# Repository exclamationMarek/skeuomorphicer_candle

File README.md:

# Skeuomorphicer Candle

A more skeuomorphic LED candle, one that you turn on with a flame, and off with a blow, like a real candle!
Super simple design with no microcontrollers, op-amps nor any other integrated circuits. Just one transistor, one thermistor and a couple of passives.

As seen on youtube, here: [https://www.youtube.com/watch?v=r8O8MNvkZiY](https://www.youtube.com/watch?v=r8O8MNvkZiY)

# How it works

* Heating the NTC thermistor makes its resistance drop, which increases the voltage on the MOSFET gate and turns on the bulb
* The current limiting R2 resistor gets hot
* The PCB is carefully designed to thermally connect R2 to the NTC
* Heat from R2 makes the NTC hot, so it stays hot even when the flame is removed
* This keeps the candle on
* Once you blow on the PCB, the heat is removed, breaking the cycle and turning off the light
* Yes, the schematic looks like a candle

* The current limiting (and heat producing) resistor is doubled, to surround the NTC on both sides
* They also share an electrical connection with the NTC - the VCC node (on top)
* That VCC copper connection is used to transfer heat from the resistors to the NTC
* But also, is wide and exposed to being blown at
* This is a finicky design challenge that required iterative fine tuning
* The current implementation works best with about 0.1W (total) dissipated on the heating resistors, which keeps the NTC at about 55°C
* Testd on a 1.0mm 2-layer PCB with 35um copper foil. Tested with black solder mask (it might make a difference?)

Note that this is the simplified schematic that omits the power supply. In real application, the varying voltage of batteries causes the circuit to be unreliable. With a full battery, the NTC runs too hot, making the candle difficult to blow out, and with a low battery it runs too cool, turning itself off unprompted. To fix this, the recommended design adds a voltage regulator (boost converter) to keep VCC stable and the candle reliable.

# PCB design available in 4 variants:
## [Minimal](Skeuomorphic_candle_minimal)
* Designed for 1.5V mini light bulb and 2xAA batteries
* Very low component count
* Does not work with LEDs!
* No ICs. Just 1 NMOS, 1 NTC and some resistors
* If you want the simplest skeuomorphicer candle, use this PCB.
* Alternatively, use with external 3.3V regulated supply

## [Basic - recommended](Skeuomorphic_candle_basic)
* Works great with a mini light bulb and OK-ish with LEDs
* Supports various batteries
* Low component count, but requires power regulator IC
* If you want to make a resonably well working skeuomorphicer candle, use this PCB

## [Custom](Skeuomorphic_candle_custom)
* PCB with extra footprints for implementation flexibility
* Can be configured as either the "Minimal" or "Basic" variant
* Can be configured as bulb + LEDs
* LED brightness can be adjusted, while maintaining reliable flame detection
* Has test points
* If you want to experiment with the design, use this PCB

## [Digital](Skeuomorphic_candle_digital)
* EWWWW digital microcontroller!
* 32bits?! For like one 'if' statement?!
* 2KB of RAM?! You can fly to the bloody moon on 2KB of RAM!
* If you're one of those futuristic cyberpunk chooms, use this PCB. I will try not to cry.

Detailed configuration and assembly instructions are in each PCB variant folder.

# License
This project is published under the [Creative Commons Attribution-NonCommercial 4.0 License](https://creativecommons.org/licenses/by-nc/4.0/deed.en)

Full text in license.txt

A commertial use license may be provided upon request

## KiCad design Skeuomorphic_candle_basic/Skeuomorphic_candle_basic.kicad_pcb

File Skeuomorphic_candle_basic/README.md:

# Basic Skeuomorphicer Candle
Most recommended design

# UNTESTED!
As of releasing this repo, this exact PCB design is NOT TESTED. It might be all wrong. I'm still waiting for this revision of PCBs to arrive to my lab.

# Part list (light bulb configuration)
* 1x 1.5V miniature tungsten bulb. Should draw about 100-130mA at 1.5V
* 1x SI2302 N-MOS (or similar)
* 1x ETA1061V33 boost converter with 3.3V output
* 1x 2.2uH inductor in 1008 package
* 2x 4.7uF capacitors in 0603 package
* 1x 100k NTC in 0603 package
* 2x 33R resistors in 0603 package
* 1x 6.8k resistor in 0603 package
* 1x battery holder for 2xAA
* 2x AA battery (NiMH rechargable works great)

# PCB configuration:
* 2-layer
* 1.0mm thick
* 35um (1oz) copper foil
* Basic FR4 TG135 (The candle is a bad idea and fire hazard no matter what material you pick)
* Soldermask colour may affect performance due to different emissivity. I used black to make it look like a wick.

# Assembly manual (light bulb configuration)
* Bridge Jumper JP1
* Skip D1
* Place 1.5V bulb on D2
* Use 3v3 out regulator for U1
* Populate all other components as listed in the schematic
* Find a value of R1 that makes candle work well. REDUCE if hard to blow out, INCREASE if does not stay on
* Supply from 2xAA or 2xAAA batteries
* Technically should also work with 1xAA

# Assembly manual (LED configuration)
* Use a 5V out regulator for U1
* Open Jumper JP1
* Place 2x LEDs on D1 and D2
* Populate R2 and R3 with 47-100R. Higher value produces dimmer light, but also less heat for the heat detection circut
* Populate all other components as listed in the schematic
* Find a value of R1 that makes candle work well. REDUCE if hard to blow out, INCREASE if does not stay on
* Supply from 2x or 3x AA or AAA batteries
* Technically should also work with 1xAA
* The 'custom' variant of the PCB separates the heaters from the LED current limiting resistors, which allows for dim light and reliable heat control

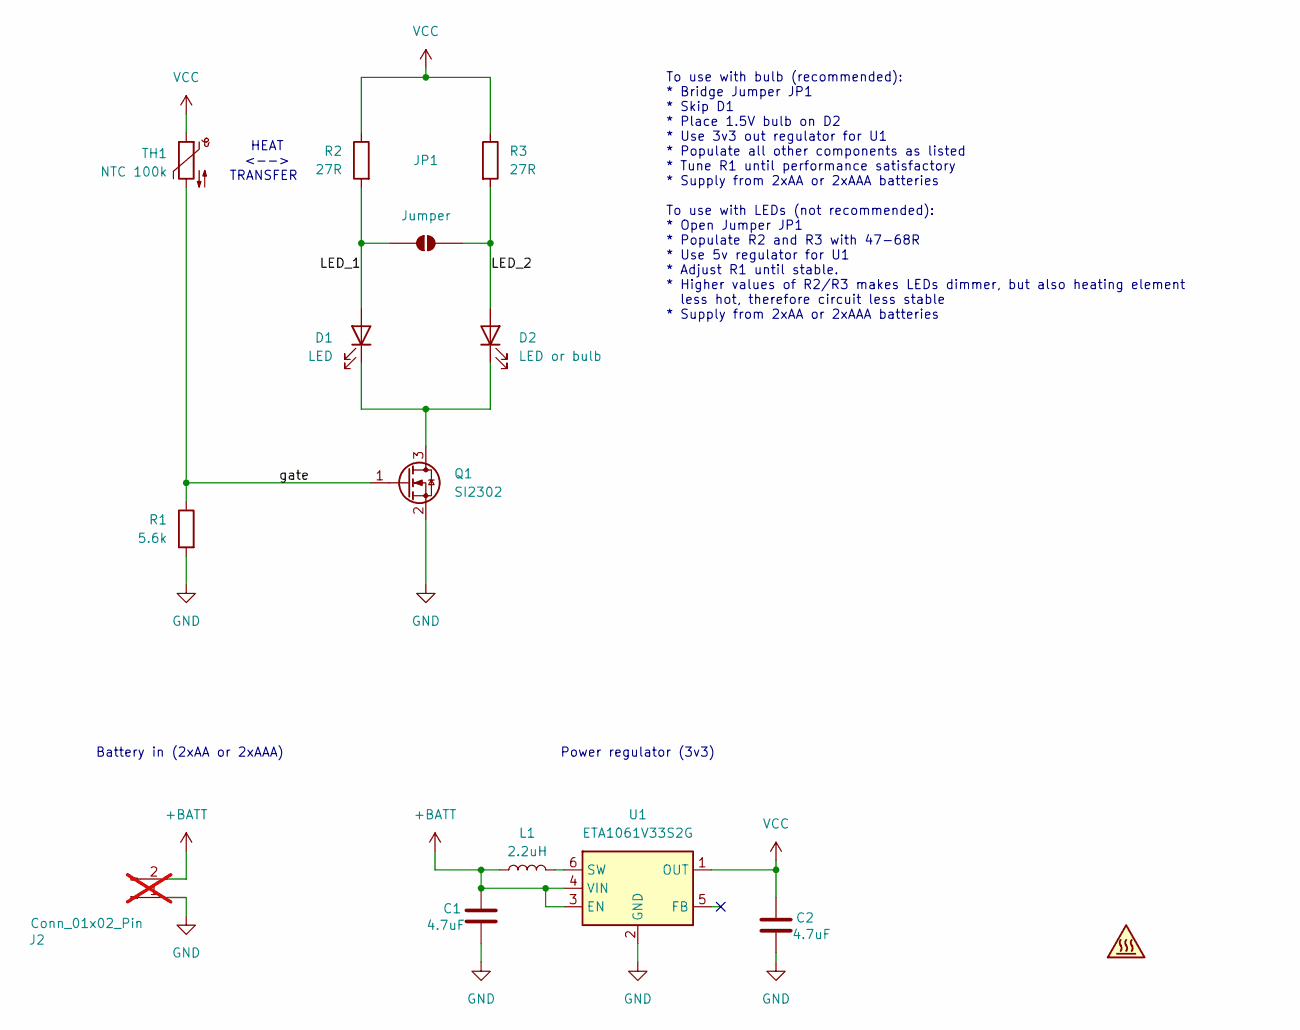
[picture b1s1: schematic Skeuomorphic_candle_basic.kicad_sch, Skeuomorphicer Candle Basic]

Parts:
C1, C2: 4.7uF; C_0603_1608Metric_Pad1.08x0.95mm_HandSolder
D1: LED; LED_PLCC_2835_Handsoldering
D2: LED or bulb; LED_PLCC_2835_Handsoldering
J2: Conn_01x02_Pin; PinHeader_1x02_P2.54mm_Vertical; not fitted
JP1: Jumper; SolderJumper-2_P1.3mm_Open_RoundedPad1.0x1.5mm
L1: 2.2uH; L_1008_2520Metric_Pad1.43x2.20mm_HandSolder; MPN WIP252012P-2R2ML
LOGO1: Logo; Skeuomorphicer_candle_logo
Q1: SI2302; SOT-23-handsoldering-smaller
R1: 5.6k; R_0603_1608Metric_Pad0.98x0.95mm_HandSolder
R2, R3: 27R; R_0603_1608Metric_Pad0.98x0.95mm_HandSolder
TH1: NTC 100k; R_0603_1608Metric_Pad0.98x0.95mm_HandSolder
U1: ETA1061V33S2G; SOT-23-6

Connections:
+BATT: C1.1, J2.2, L1.1, U1.3 (EN), U1.4 (VIN)
/LED_1: D1.2 (A), JP1.1 (A), R2.2
/LED_2: D2.2 (A), JP1.2 (B), R3.2
/gate: Q1.1 (G), R1.1, TH1.2
GND: C1.2, C2.2, J2.1, Q1.2 (S), R1.2, U1.2 (GND)
unnamed: D1.1 (K), D2.1 (K), Q1.3 (D)
unnamed: L1.2, U1.6 (SW)
VCC: C2.1, R2.1, R3.1, TH1.1, U1.1 (OUT)

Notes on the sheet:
To use with bulb (recommended): * Bridge Jumper JP1 * Skip D1 * Place 1.5V bulb on D2 * Use 3v3 out regulator for U1 * Populate all other components as listed * Tune R1 until performance satisfactory * Supply from 2xAA or 2xAAA batteries To use with LEDs (not recommended): * Open Jumper JP1 * Popul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
HEAT <--> TRANSFER
Battery in (2xAA or 2xAAA)
Power regulator (3v3)

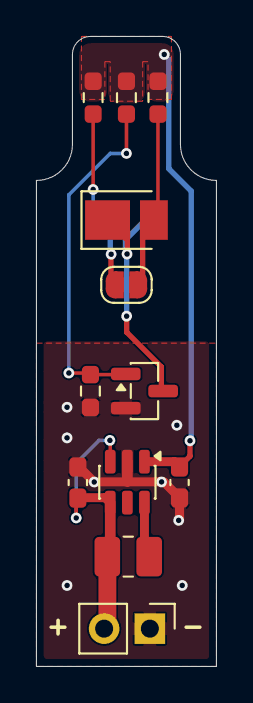
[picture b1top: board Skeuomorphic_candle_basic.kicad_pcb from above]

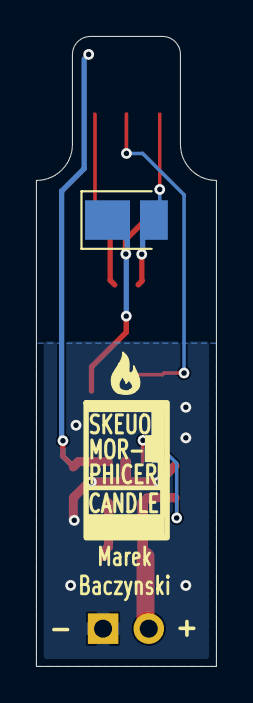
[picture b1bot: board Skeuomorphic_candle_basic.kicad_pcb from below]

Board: 2 copper layers, 10.0 x 35.0 mm, 14 parts (2 on the bottom side), 8 nets.

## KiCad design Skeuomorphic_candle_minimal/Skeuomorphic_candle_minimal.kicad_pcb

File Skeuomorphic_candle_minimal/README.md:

# Minimal Skeuomorphicer Candle
Wokrs OK, not great, but uses very few parts

# Assembly instructions

* Populate all components as shown
* Supply from 2xAA batteries (NiMH rechargable preferably)
* Test if behaves well
* If does not stay on, increase R1 (27k)
* If difficult to blow out, reduce R1 (27k)

# Sensitive to battery voltage
* This design is sensitive to battery voltage
* The lower the voltage, the more likely the candle will turn itself off
* Therefore, the candle will likely turn itself off even then there is plenty of energy left in the battery
* That is why it is best to use NiMH rechargables, otherwise you will be left with a buch of half-full batteries
* The other designs use a voltage regulator to avoid this issue

# Design relies of Vgs(th)
* This design relies on the threshold voltage of an NMOS, which is not good practice
* Be prepared to need to adjust R1 depending on your exact transistor
* It might even be necessary to tune for each transistor from the same batch
* Not a great design!

# Part list
* 1x 1.5V miniature tungsten bulb. 3mm or 4mm size, should draw about 130-160mA at 1.5V
* 1x SI2302 N-MOS (or similar. Vgs(th) should be about 0.7V)
* 1x 100k NTC thermistor in 0603 package
* 2x 22R resistors in 0603 package
* 1x 27k resistor in 0603 package
* 1x battery holder for 2xAA
* 2x AA battery (NiMH rechargable works great)

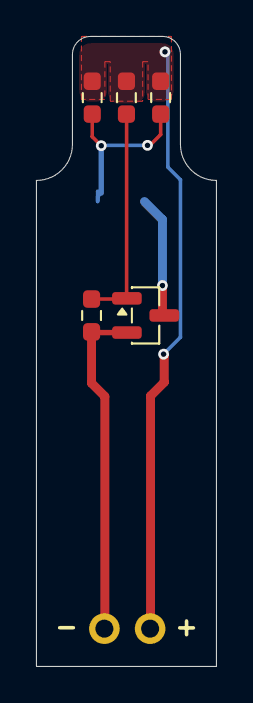
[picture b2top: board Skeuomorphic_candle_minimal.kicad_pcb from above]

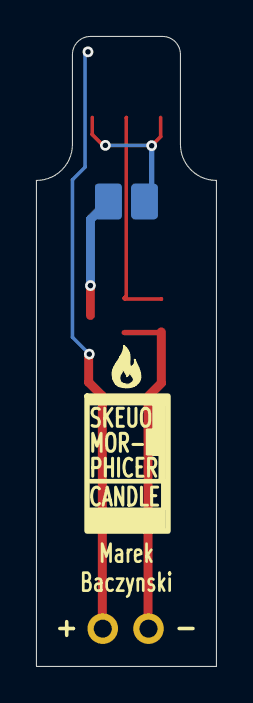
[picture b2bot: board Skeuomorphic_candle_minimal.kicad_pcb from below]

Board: 2 copper layers, 10.0 x 35.0 mm, 8 parts (2 on the bottom side), 5 nets.

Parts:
D1: BULB; Mini_bulb_flat
J2: Conn_01x02_Pin; PinHeader_1x02_P2.54mm_Vertical
LOGO1: Logo; Skeuomorphicer_candle_logo
Q1: SI2302; SOT-23-handsoldering-smaller
R1: 27k; R_0603_1608Metric_Pad0.98x0.95mm_HandSolder
R2, R3: 11R; R_0603_1608Metric_Pad0.98x0.95mm_HandSolder
TH1: NTC 100k; R_0603_1608Metric_Pad0.98x0.95mm_HandSolder

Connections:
+BATT: J2.2, R2.1, R3.1, TH1.1
/NTC_low: Q1.1 (G), R1.1, TH1.2
GND: J2.1, Q1.2 (S), R1.2
unnamed: D1.2 (A), R2.2, R3.2
unnamed: D1.1 (K), Q1.3 (D)

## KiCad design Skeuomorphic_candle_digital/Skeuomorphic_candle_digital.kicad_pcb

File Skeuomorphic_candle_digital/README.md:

# Digital Skeuomorphicer Candle
For when you just have to put code into everything

# UNTESTED!
As of releasing this repo, this PCB design is NOT TESTED. It might be all wrong.

# Part list
* CH32V003J4M6 microcontroller in SOP-8 package
* 100k NTC in 0603
* SI2302 NMOS (or similar)
* 1uF capacitor in 0603 for the MCU
* 3V miniature tungsten bulb, or 2x 2835 LEDs
* Some 0603 resistors
* Optionally some 0603 LEDs
* 3xAA or 3xAAA battery holder or 1x LiPo battery

# Firmware
Firmware for the Digital Skeuomorphicer Candle is comming soon. Probably.

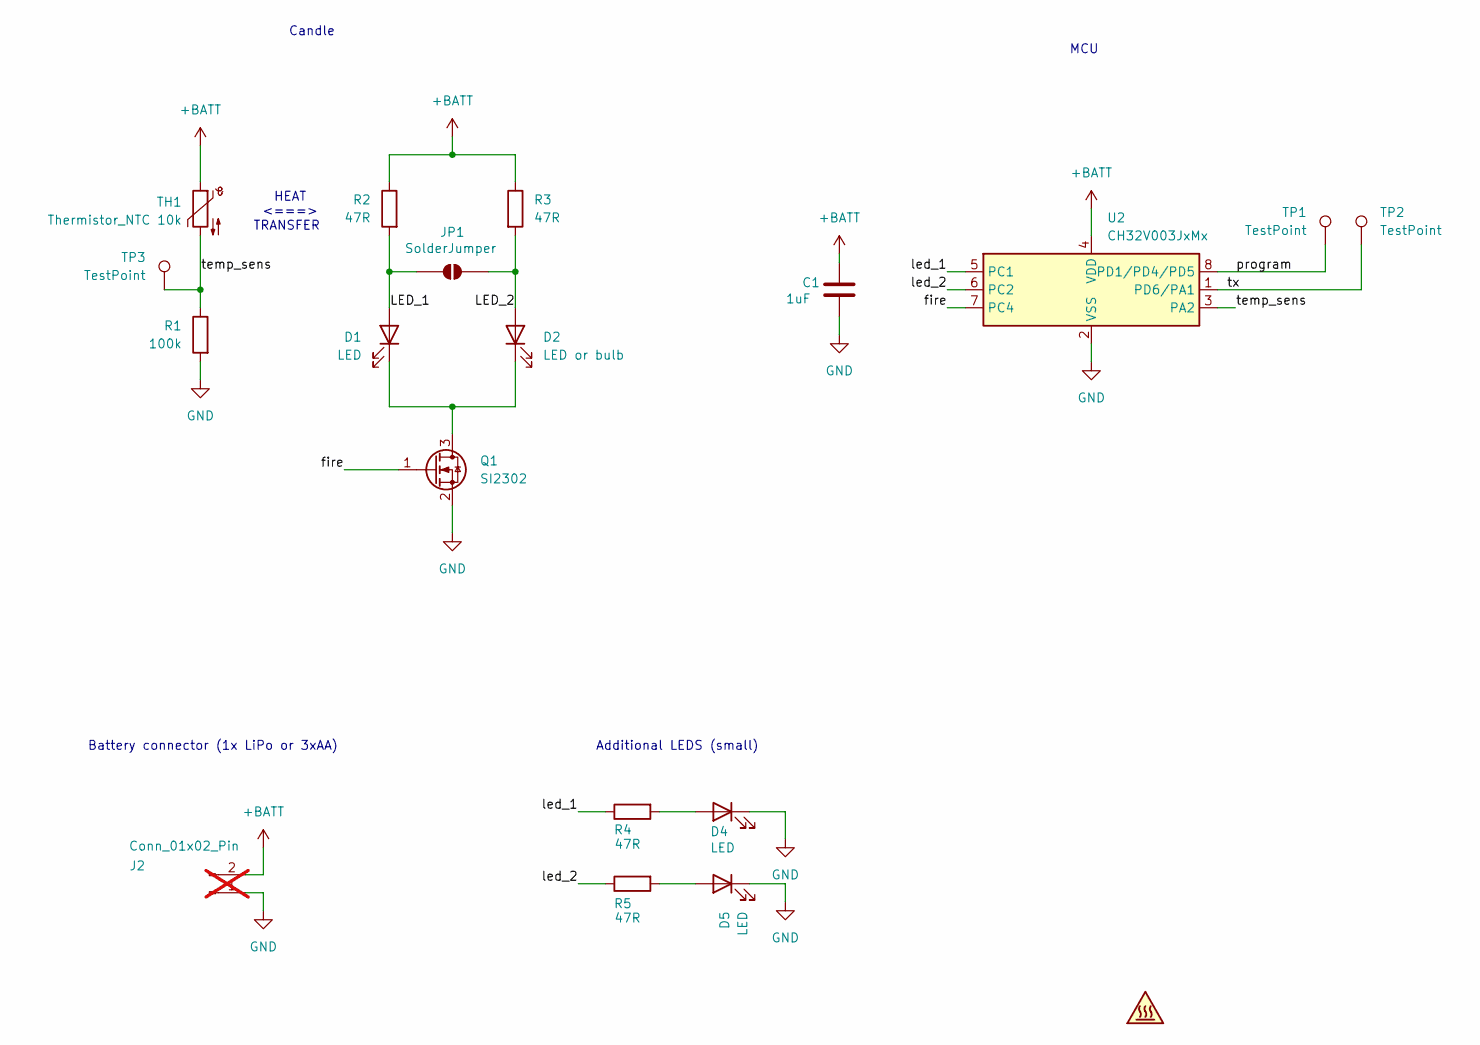
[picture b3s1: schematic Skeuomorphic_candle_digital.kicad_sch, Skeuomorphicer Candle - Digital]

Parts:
C1: 1uF; C_0603_1608Metric_Pad1.08x0.95mm_HandSolder
D1: LED; LED_PLCC_2835_Handsoldering
D2: LED or bulb; LED_PLCC_2835_Handsoldering
D4, D5: LED; LED_0603_1608Metric_Pad1.05x0.95mm_HandSolder
J2: Conn_01x02_Pin; PinHeader_1x02_P2.54mm_Vertical; not fitted
JP1: SolderJumper; SolderJumper-2_P1.3mm_Open_RoundedPad1.0x1.5mm
LOGO1: Logo; Skeuomorphicer_candle_logo
Q1: SI2302; SOT-23-handsoldering-smaller
R1: 100k; R_0603_1608Metric_Pad0.98x0.95mm_HandSolder
R2, R3, R4, R5: 47R; R_0603_1608Metric_Pad0.98x0.95mm_HandSolder
TH1: Thermistor_NTC 10k; R_0603_1608Metric_Pad0.98x0.95mm_HandSolder
TP1, TP2, TP3: TestPoint; TestPoint_Pad_D1.0mm
U2: CH32V003JxMx; JEITA_SOIC-8_3.9x4.9mm_P1.27mm

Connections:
+BATT: C1.1, J2.2, R2.1, R3.1, TH1.1, U2.4 (VDD)
/LED_1: D1.2 (A), JP1.1 (A), R2.2
/LED_2: D2.2 (A), JP1.2 (B), R3.2
/fire: Q1.1 (G), U2.7 (PC4)
/led_1: R4.1, U2.5 (PC1)
/led_2: R5.1, U2.6 (PC2)
/program: TP1.1 (1_1), U2.8 (PD1/PD4/PD5)
/temp_sens: R1.1, TH1.2, TP3.1 (1_1), U2.3 (PA2)
/tx: TP2.1 (1_1), U2.1 (PD6/PA1)
GND: C1.2, D4.1 (K), D5.1 (K), J2.1, Q1.2 (S), R1.2, U2.2 (VSS)
unnamed: D1.1 (K), D2.1 (K), Q1.3 (D)
unnamed: D4.2 (A), R4.2
unnamed: D5.2 (A), R5.2

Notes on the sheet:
MCU
Battery connector (1x LiPo or 3xAA)
HEAT <===> TRANSFER
Additional LEDS (small)
Candle

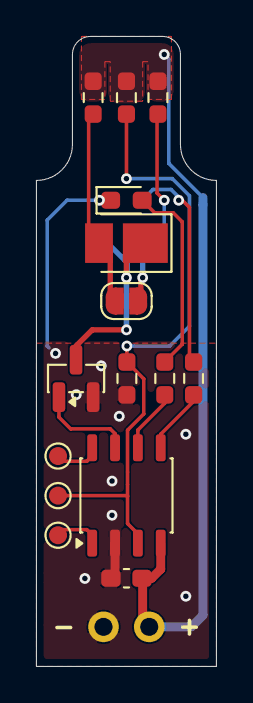
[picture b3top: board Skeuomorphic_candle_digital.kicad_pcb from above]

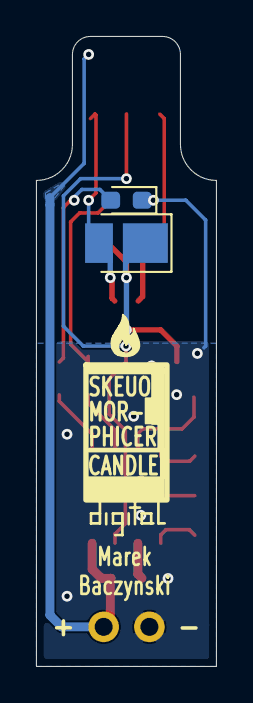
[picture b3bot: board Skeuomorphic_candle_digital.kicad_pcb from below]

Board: 2 copper layers, 10.0 x 35.0 mm, 19 parts (3 on the bottom side), 13 nets.

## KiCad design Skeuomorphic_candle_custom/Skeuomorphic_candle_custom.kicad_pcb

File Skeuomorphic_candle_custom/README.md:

# Custom Skeuomorphicer Candle
For when you want to experiment with the design

# UNTESTED!
As of releasing this repo, this PCB design is NOT TESTED. It might be all wrong.

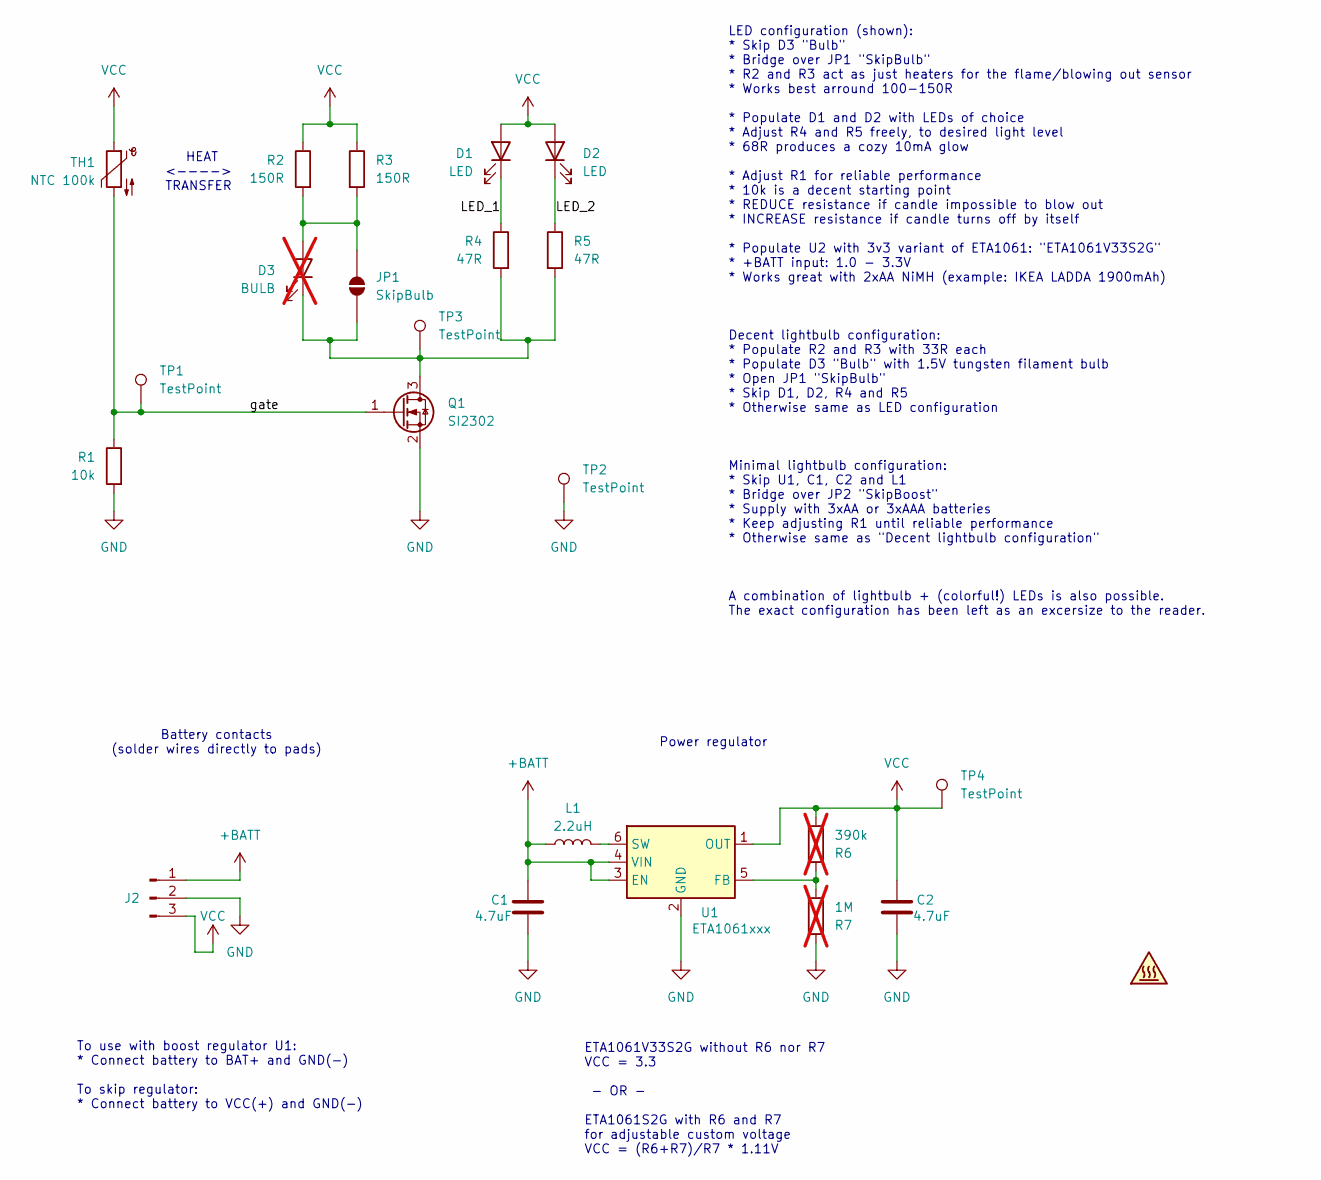
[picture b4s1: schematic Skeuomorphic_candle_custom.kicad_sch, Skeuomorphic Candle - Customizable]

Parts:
C1, C2: 4.7uF; C_0603_1608Metric_Pad1.08x0.95mm_HandSolder
D1, D2: LED; LED_PLCC_2835_Handsoldering
D3: BULB; Mini_bulb_flat; not fitted
J2: Conn_01x03_Pin; PinHeader_1x03_P2.54mm_Vertical
JP1: SkipBulb; SolderJumper-2_P1.3mm_Open_RoundedPad1.0x1.5mm
L1: 2.2uH; L_1008_2520Metric_Pad1.43x2.20mm_HandSolder; MPN INPAQ WIP252012P-2R2ML
LOGO1: Logo; Skeuomorphicer_candle_logo
Q1: SI2302; SOT-23-handsoldering-smaller
R1: 10k; R_0603_1608Metric_Pad0.98x0.95mm_HandSolder
R2, R3: 150R; R_0603_1608Metric_Pad0.98x0.95mm_HandSolder
R4, R5: 47R; R_0603_1608Metric_Pad0.98x0.95mm_HandSolder
R6: 390k; R_0603_1608Metric_Pad0.98x0.95mm_HandSolder; not fitted
R7: 1M; R_0603_1608Metric_Pad0.98x0.95mm_HandSolder; not fitted
TH1: NTC 100k; R_0603_1608Metric_Pad0.98x0.95mm_HandSolder
TP1, TP2, TP3, TP4: TestPoint; TestPoint_Pad_D1.0mm
U1: ETA1061xxx; SOT-23-6; MPN ETA1061V33S2G

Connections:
+BATT: C1.1, J2.1, L1.1, U1.3 (EN), U1.4 (VIN)
/LED_1: D1.1 (K), R4.1
/LED_2: D2.1 (K), R5.1
/gate: Q1.1 (G), R1.1, TH1.2, TP1.1 (1_1)
GND: C1.2, C2.2, J2.2, Q1.2 (S), R1.2, R7.1, TP2.1 (1_1), U1.2 (GND)
unnamed: D3.2 (A), JP1.2 (B), R2.2, R3.2
unnamed: D3.1 (K), JP1.1 (A), Q1.3 (D), R4.2, R5.2, TP3.1 (1_1)
unnamed: R6.1, R7.2, U1.5 (FB)
unnamed: L1.2, U1.6 (SW)
VCC: C2.1, D1.2 (A), D2.2 (A), J2.3, R2.1, R3.1, R6.2, TH1.1, TP4.1 (1_1), U1.1 (OUT)

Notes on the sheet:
Battery contacts (solder wires directly to pads)
To use with boost regulator U1: * Connect battery to BAT+ and GND(-) To skip regulator: * Connect battery to VCC(+) and GND(-)
Power regulator
ETA1061V33S2G without R6 nor R7 VCC = 3.3 - OR - ETA1061S2G with R6 and R7 for adjustable custom voltage VCC = (R6+R7)/R7 * 1.11V
LED configuration (shown): * Skip D3 "Bulb" * Bridge over JP1 "SkipBulb" * R2 and R3 act as just heaters for the flame/blowing out sensor * Works best arround 100-150R * Populate D1 and D2 with LEDs of choice * Adjust R4 and R5 freely, to desired light level * 68R produces a cozy 10mA glow * Adjust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
HEAT <----> TRANSFER

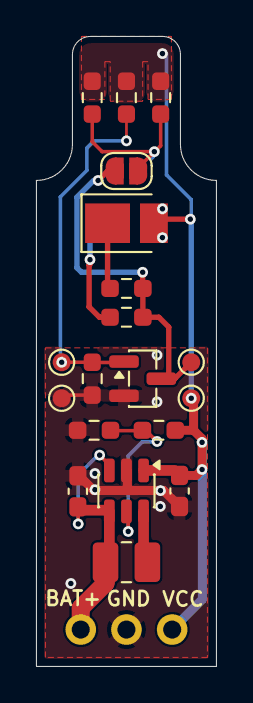
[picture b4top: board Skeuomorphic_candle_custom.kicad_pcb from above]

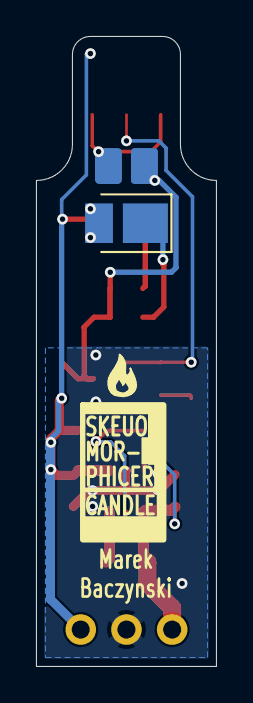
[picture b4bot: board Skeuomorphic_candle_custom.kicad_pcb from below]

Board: 2 copper layers, 10.0 x 35.0 mm, 23 parts (3 on the bottom side), 10 nets.
